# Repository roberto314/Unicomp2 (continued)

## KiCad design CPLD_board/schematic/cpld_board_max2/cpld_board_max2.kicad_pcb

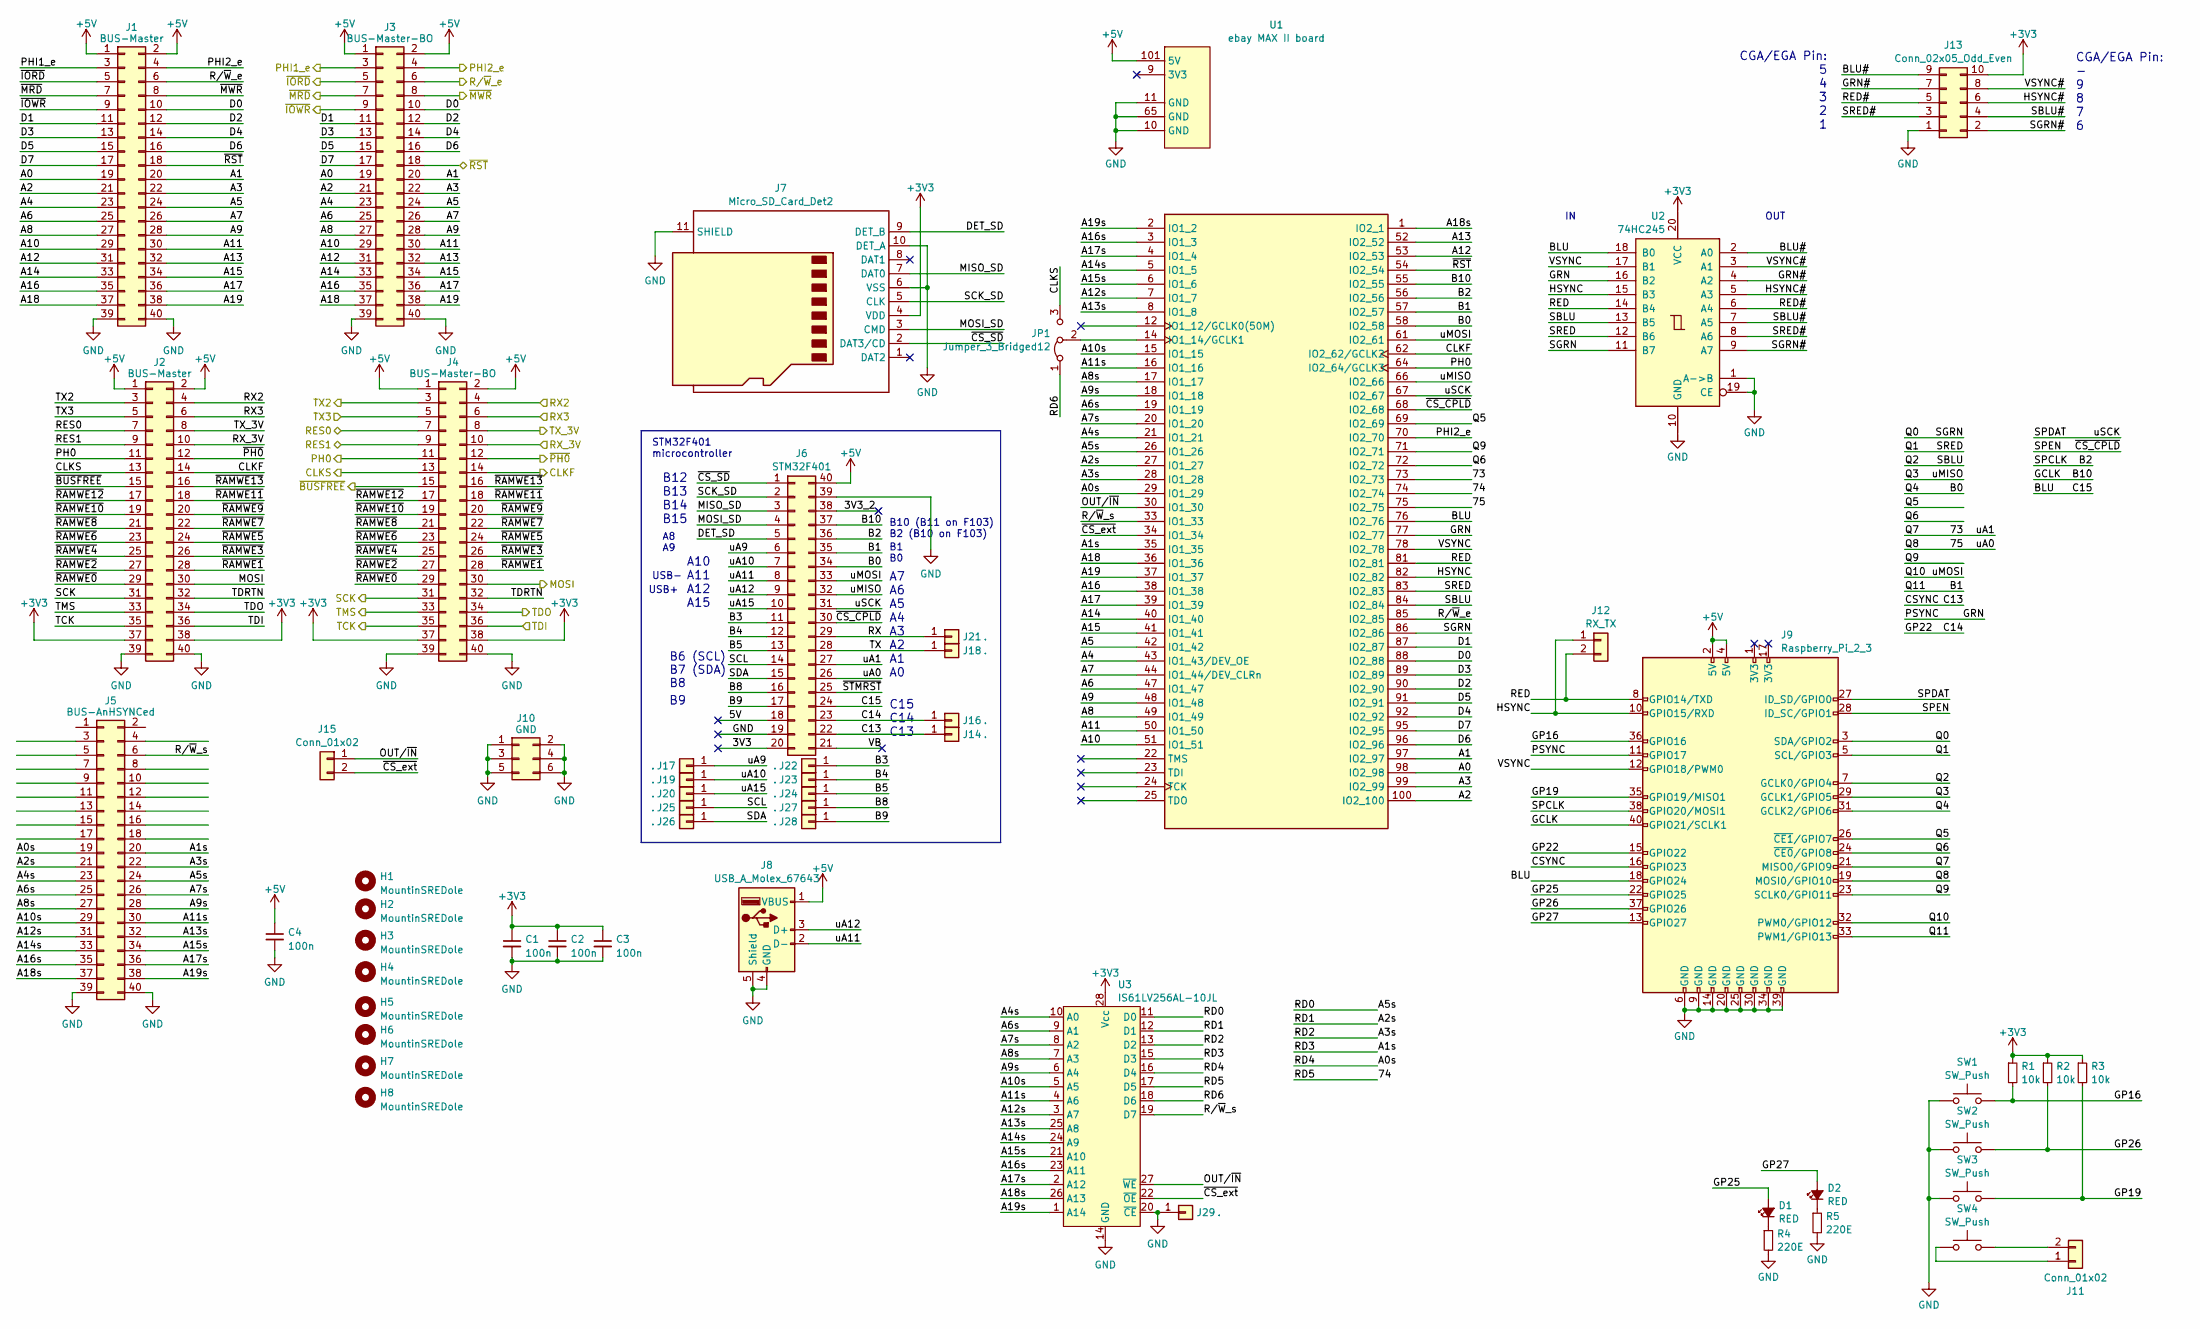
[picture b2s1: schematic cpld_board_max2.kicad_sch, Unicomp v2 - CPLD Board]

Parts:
C1, C2, C3, C4: 100n; C_1206_3216Metric
D1, D2: RED; LED_D3.0mm
H1, H2, H3, H4, H5, H6, H7, H8: MountinSREDole; MountingHole_3.2mm_M3
J1, J2: BUS-Master; PinSocket_2x20_P2.54mm_Vertical
J3, J4: BUS-Master-BO; PinSocket_2x20_P2.54mm_Vertical
J5: BUS-AnHSYNCed; PinHeader_2x20_P2.54mm_Horizontal
J6: STM32F401; DIP-40_W15.24mm_Socket_LongPads
J7: Micro_SD_Card_Det2; microSD_HC_Hirose_DM3D-SF
J8: USB_A_Molex_67643; USB_A_Molex_67643_Horizontal
J9: Raspberry_Pi_2_3; Raspberry_Pi_Zero_Socketed_THT_FaceDown_MountingHoles
J10: GND; PinHeader_2x03_P2.54mm_Vertical
J11, J15: Conn_01x02; PinHeader_1x02_P2.54mm_Vertical
J12: RX_TX; PinHeader_1x02_P2.54mm_Vertical
J13: Conn_02x05_Odd_Even; PinHeader_2x05_P2.54mm_Vertical
J14, J16, J17, J18, J19, J20, J21, J22, J23, J24, J25, J26, J27, J28, J29: .; PinHeader_1x01_P2.00mm_Vertical
JP1: Jumper_3_Bridged12; SolderJumper-3_P1.3mm_Bridged12_RoundedPad1.0x1.5mm
R1, R2, R3: 10k; R_1206_3216Metric_Pad1.30x1.75mm_HandSolder
R4, R5: 220E; R_1206_3216Metric_Pad1.30x1.75mm_HandSolder
SW1, SW2, SW3, SW4: SW_Push; SW_PUSH_6mm_H4.3mm
U1: ebay MAX II board; ebay-MAX_II_board
U2: 74HC245; SO-20_5.3x12.6mm_P1.27mm
U3: IS61LV256AL-10JL; SOIC-28W_7.5x17.9mm_P1.27mm

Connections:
+3V3: C1.1, C2.1, C3.1, J2.37, J2.38, J4.37, J4.38, J7.4 (VDD), J13.10, R1.1, R2.1, R3.1, U2.20 (VCC), U3.28 (Vcc)
+5V: C4.1, J1.1, J1.2, J2.1, J2.2, J3.1, J3.2, J4.1, J4.2, J6.40, J8.1 (VBUS), J9.2 (5V), J9.4 (5V), U1.101 (5V)
/3V3: J6.20
/3V3_2: J6.38
/5V: J6.18
/73: J6.27, J9.21 (MISO0/GPIO9), U1.73 (IO2_73)
/74: U1.74 (IO2_74), U3.17 (D5)
/75: J6.26, J9.19 (MOSI0/GPIO10), U1.75 (IO2_75)
/A0: J1.19, J3.19, U1.98 (IO2_98)
/A0s: J5.19, U1.29 (IO1_29), U3.16 (D4)
/A1: J1.20, J3.20, U1.97 (IO2_97)
/A1s: J5.20, U1.35 (IO1_35), U3.15 (D3)
/A2: J1.21, J3.21, U1.100 (IO2_100)
/A2s: J5.21, U1.27 (IO1_27), U3.12 (D1)
/A3: J1.22, J3.22, U1.99 (IO2_99)
/A3s: J5.22, U1.28 (IO1_28), U3.13 (D2)
/A4: J1.23, J3.23, U1.43 (IO1_43/DEV_OE)
/A4s: J5.23, U1.21 (IO1_21), U3.10 (A0)
/A5: J1.24, J3.24, U1.42 (IO1_42)
/A5s: J5.24, U1.26 (IO1_26), U3.11 (D0)
/A6: J1.25, J3.25, U1.47 (IO1_47)
/A6s: J5.25, U1.19 (IO1_19), U3.9 (A1)
/A7: J1.26, J3.26, U1.44 (IO1_44/DEV_CLRn)
/A7s: J5.26, U1.20 (IO1_20), U3.8 (A2)
/A8: J1.27, J3.27, U1.49 (IO1_49)
/A8s: J5.27, U1.17 (IO1_17), U3.7 (A3)
/A9: J1.28, J3.28, U1.48 (IO1_48)
/A9s: J5.28, U1.18 (IO1_18), U3.6 (A4)
/A10: J1.29, J3.29, U1.51 (IO1_51)
/A10s: J5.29, U1.15 (IO1_15), U3.5 (A5)
/A11: J1.30, J3.30, U1.50 (IO1_50)
/A11s: J5.30, U1.16 (IO1_16), U3.4 (A6)
/A12: J1.31, J3.31, U1.53 (IO2_53)
/A12s: J5.31, U1.7 (IO1_7), U3.3 (A7)
/A13: J1.32, J3.32, U1.52 (IO2_52)
/A13s: J5.32, U1.8 (IO1_8), U3.25 (A8)
/A14: J1.33, J3.33, U1.40 (IO1_40)
/A14s: J5.33, U1.5 (IO1_5), U3.24 (A9)
/A15: J1.34, J3.34, U1.41 (IO1_41)
/A15s: J5.34, U1.6 (IO1_6), U3.21 (A10)
/A16: J1.35, J3.35, U1.38 (IO1_38)
/A16s: J5.35, U1.3 (IO1_3), U3.23 (A11)
/A17: J1.36, J3.36, U1.39 (IO1_39)
/A17s: J5.36, U1.4 (IO1_4), U3.2 (A12)
/A18: J1.37, J3.37, U1.36 (IO1_36)
/A18s: J5.37, U1.1 (IO2_1), U3.26 (A13)
/A19: J1.38, J3.38, U1.37 (IO1_37)
/A19s: J5.38, U1.2 (IO1_2), U3.1 (A14)
/B0: J6.34, J9.31 (GCLK2/GPIO6), U1.58 (IO2_58)
/B1: J6.35, J9.33 (PWM1/GPIO13), U1.57 (IO2_57)
/B2: J6.36, J9.38 (GPIO20/MOSI1), U1.56 (IO2_56)
/B3: J6.11, J22.1
/B4: J6.12, J23.1
/B5: J6.13, J24.1
/B8: J6.16, J27.1
/B9: J6.17, J28.1
/B10: J6.37, J9.40 (GPIO21/SCLK1), U1.55 (IO2_55)
/BLU: J6.24, J9.18 (GPIO24), U1.76 (IO2_76), U2.18 (B0)
/BLU#: J13.9, U2.2 (A0)
/C13: J6.22, J9.16 (GPIO23), J14.1
/C14: J6.23, J9.15 (GPIO22), J16.1
/CLKF: J2.14, J4.14, U1.62 (IO2_62/GCLK2)
/CLKS: J2.13, J4.13, JP1.3 (B)
/D0: J1.10, J3.10, U1.88 (IO2_88)
/D1: J1.11, J3.11, U1.87 (IO2_87)
/D2: J1.12, J3.12, U1.90 (IO2_90)
/D3: J1.13, J3.13, U1.89 (IO2_89)
/D4: J1.14, J3.14, U1.92 (IO2_92)
/D5: J1.15, J3.15, U1.91 (IO2_91)
/D6: J1.16, J3.16, U1.96 (IO2_96)
/D7: J1.17, J3.17, U1.95 (IO2_95)
/DET_SD: J6.5, J7.9 (DET_B)
/GP16: J9.36 (GPIO16), R1.2, SW1.2
/GP19: J9.35 (GPIO19/MISO1), R3.2, SW3.2
/GP25: D1.2 (A), J9.22 (GPIO25)
/GP26: J9.37 (GPIO26), R2.2, SW2.2
/GP27: D2.2 (A), J9.13 (GPIO27)
/GRN: J9.11 (GPIO17), U1.77 (IO2_77), U2.16 (B2)
/GRN#: J13.7, U2.4 (A2)
/HSYNC: J9.10 (GPIO15/RXD), J12.1, U1.82 (IO2_82), U2.15 (B3)
/HSYNC#: J13.6, U2.5 (A3)
/MISO_SD: J6.3, J7.7 (DAT0)
/MOSI: J2.30, J4.30
/MOSI_SD: J6.4, J7.3 (CMD)
/OUT/~IN: J15.1, U1.30 (IO1_30), U3.27 (~WE)
/PH0: J2.11, J4.11, U1.64 (IO2_64/GCLK3)
/PHI1_e: J1.3, J3.3
/PHI2_e: J1.4, J3.4, U1.70 (IO2_70)
/Q0: J9.3 (SDA/GPIO2), U1.86 (IO2_86), U2.11 (B7)
/Q1: J9.5 (SCL/GPIO3), U1.83 (IO2_83), U2.12 (B6)
/Q2: J9.7 (GCLK0/GPIO4), U1.84 (IO2_84), U2.13 (B5)
/Q3: J6.32, J9.29 (GCLK1/GPIO5), U1.66 (IO2_66)
/Q5: J9.26 (~CE1/GPIO7), U1.69 (IO2_69)
/Q6: J9.24 (~CE0/GPIO8), U1.72 (IO2_72)
/Q9: J9.23 (SCLK0/GPIO11), U1.71 (IO2_71)
/Q10: J6.33, J9.32 (PWM0/GPIO12), U1.61 (IO2_61)
/RD6: JP1.1 (A), U3.18 (D6)
/RED: J9.8 (GPIO14/TXD), J12.2, U1.81 (IO2_81), U2.14 (B4)
/RED#: J13.5, U2.6 (A4)
/RES0: J2.7, J4.7
/RES1: J2.9, J4.9
/RX: J6.29, J21.1; also elsewhere on the board
/RX2: J2.4, J4.4
/RX3: J2.6, J4.6
/RX_3V: J2.10, J4.10
/R/~W_e: J1.6, J3.6, U1.85 (IO2_85)
/R/~W_s: J5.6, U1.33 (IO1_33), U3.19 (D7)
/SBLU#: J13.4, U2.7 (A5)
/SCK: J2.31, J4.31
/SCK_SD: J6.2, J7.5 (CLK)
/SCL: J6.14, J25.1
/SDA: J6.15, J26.1
/SGRN#: J13.2, U2.9 (A7)
/SPDAT: J6.31, J9.27 (ID_SD/GPIO0), U1.67 (IO2_67)
/SPEN: J6.30, J9.28 (ID_SC/GPIO1), U1.68 (IO2_68)
/SRED#: J13.3, U2.8 (A6)
/TCK: J2.35, J4.35
/TDI: J2.36, J4.36
/TDO: J2.34, J4.34
/TDRTN: J2.32, J4.32
/TMS: J2.33, J4.33
/TX: J6.28, J18.1
/TX2: J2.3, J4.3
/TX3: J2.5, J4.5
/TX_3V: J2.8, J4.8
/VB: J6.21
/VSYNC: J9.12 (GPIO18/PWM0), U1.78 (IO2_78), U2.17 (B1)
/VSYNC#: J13.8, U2.3 (A1)
/uA9: J6.6, J17.1
/uA10: J6.7, J19.1
/uA11: J6.8, J8.2 (D-)
/uA12: J6.9, J8.3 (D+)
/uA15: J6.10, J20.1
/~BUSFREE: J2.15, J4.15
/~CS_SD: J6.1, J7.2 (DAT3/CD)
/~CS_ext: J15.2, U1.34 (IO1_34), U3.22 (~OE)
/~IORD: J1.5, J3.5
/~IOWR: J1.9, J3.9
/~MRD: J1.7, J3.7
/~MWR: J1.8, J3.8
/~PH0: J2.12, J4.12
/~RAMWE0: J2.29, J4.29
/~RAMWE1: J2.28, J4.28
/~RAMWE2: J2.27, J4.27
/~RAMWE3: J2.26, J4.26
/~RAMWE4: J2.25, J4.25
/~RAMWE5: J2.24, J4.24
/~RAMWE6: J2.23, J4.23
/~RAMWE7: J2.22, J4.22
/~RAMWE8: J2.21, J4.21
/~RAMWE9: J2.20, J4.20
/~RAMWE10: J2.19, J4.19
/~RAMWE11: J2.18, J4.18
/~RAMWE12: J2.17, J4.17
/~RAMWE13: J2.16, J4.16
/~RST: J1.18, J3.18, U1.54 (IO2_54)
/~STMRST: J6.25
GND: C1.2, C2.2, C3.2, C4.2, J1.39, J1.40, J2.39, J2.40, J3.39, J3.40, J4.39, J4.40, J5.39, J5.40, J6.19, J6.39, J7.6 (VSS), J7.10 (DET_A), J7.11 (SHIELD), J8.4 (GND), J8.5 (Shield), J9.6 (GND), J9.9 (GND), J9.14 (GND), J9.20 (GND), J9.25 (GND), J9.30 (GND), J9.34 (GND), J9.39 (GND), J10.1, J10.2, J10.3, J10.4, J10.5, J10.6, J13.1, J29.1, R4.2, R5.2, SW1.1, SW2.1, SW3.1, U1.10 (GND), U1.11 (GND), U1.65 (GND), U2.1 (A->B), U2.10 (GND), U2.19 (CE), U3.14 (GND), U3.20 (~CE)
unnamed: D1.1 (K), R4.1
unnamed: D2.1 (K), R5.1
unnamed: J11.1, SW4.1
unnamed: J11.2, SW4.2
unnamed: JP1.2 (C), U1.14 (IO1_14/GCLK1)

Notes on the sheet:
OUT
USB+
STM32F401 microcontroller
B1 B0
CGA/EGA Pin: 5 4 3 2 1
A7 A6 A5 A4 A3 A2 A1 A0
B6 (SCL) B7 (SDA) B8
CGA/EGA Pin: - 9 8 7 6
B12 B13 B14 B15
A8 A9
C15 C14 C13
USB-
B10 (B11 on F103) B2 (B10 on F103)
A10 A11 A12 A15

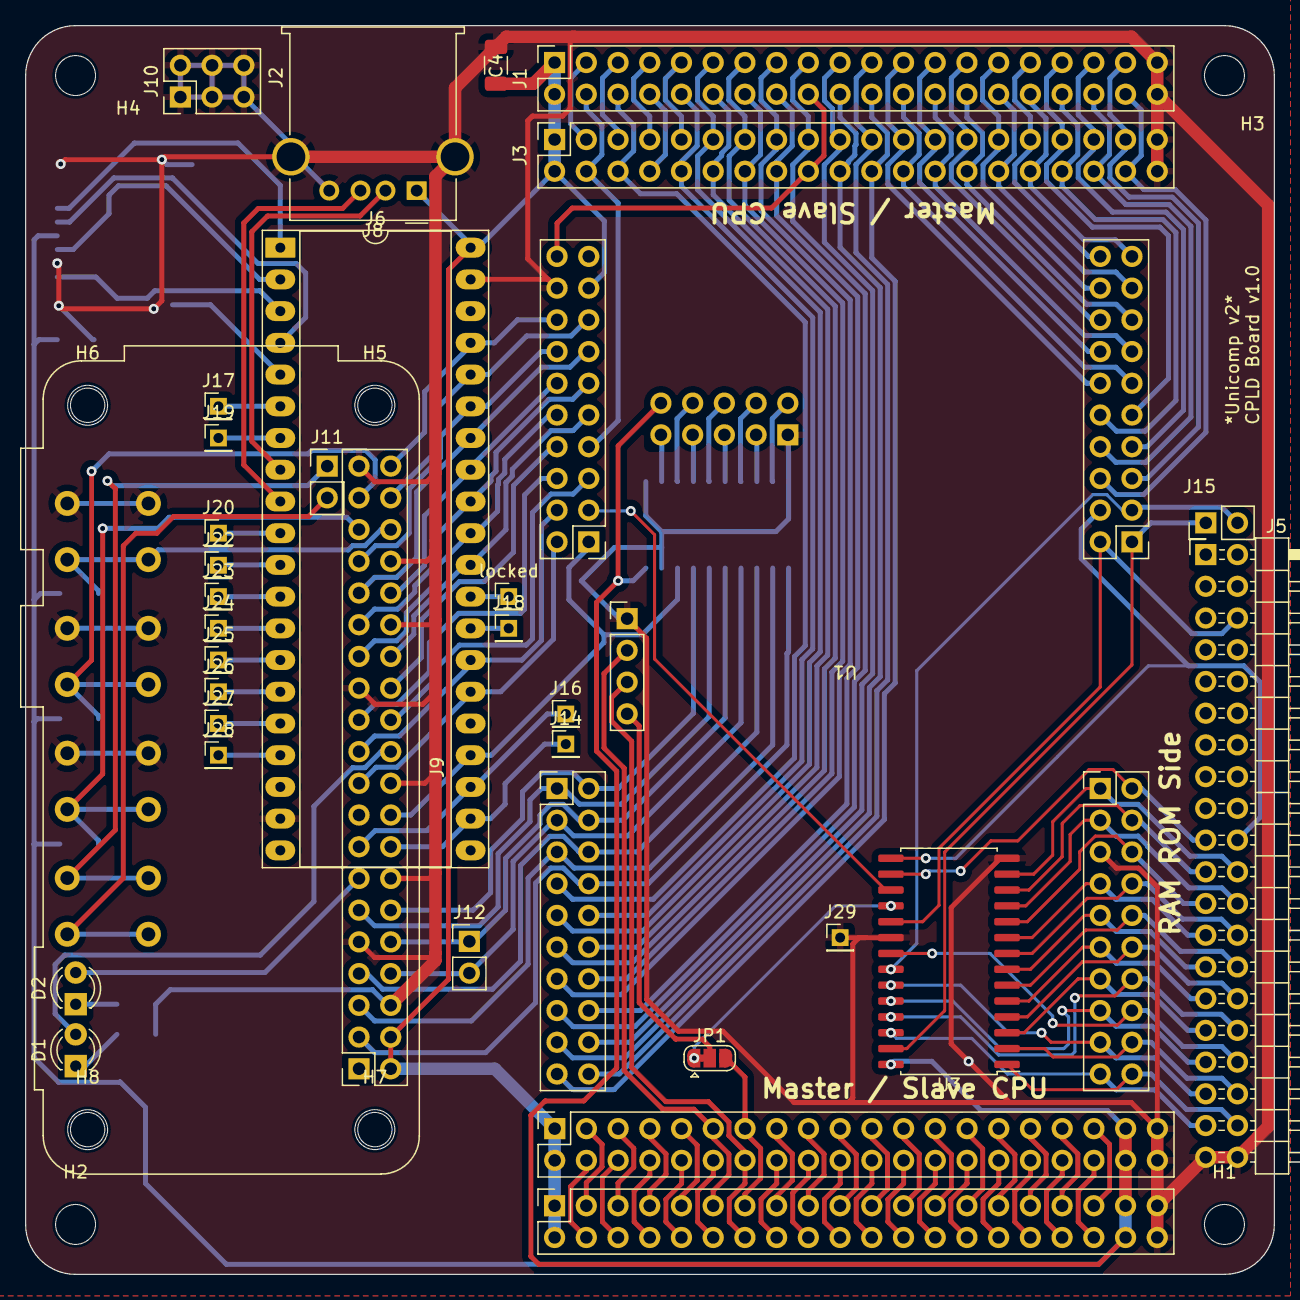
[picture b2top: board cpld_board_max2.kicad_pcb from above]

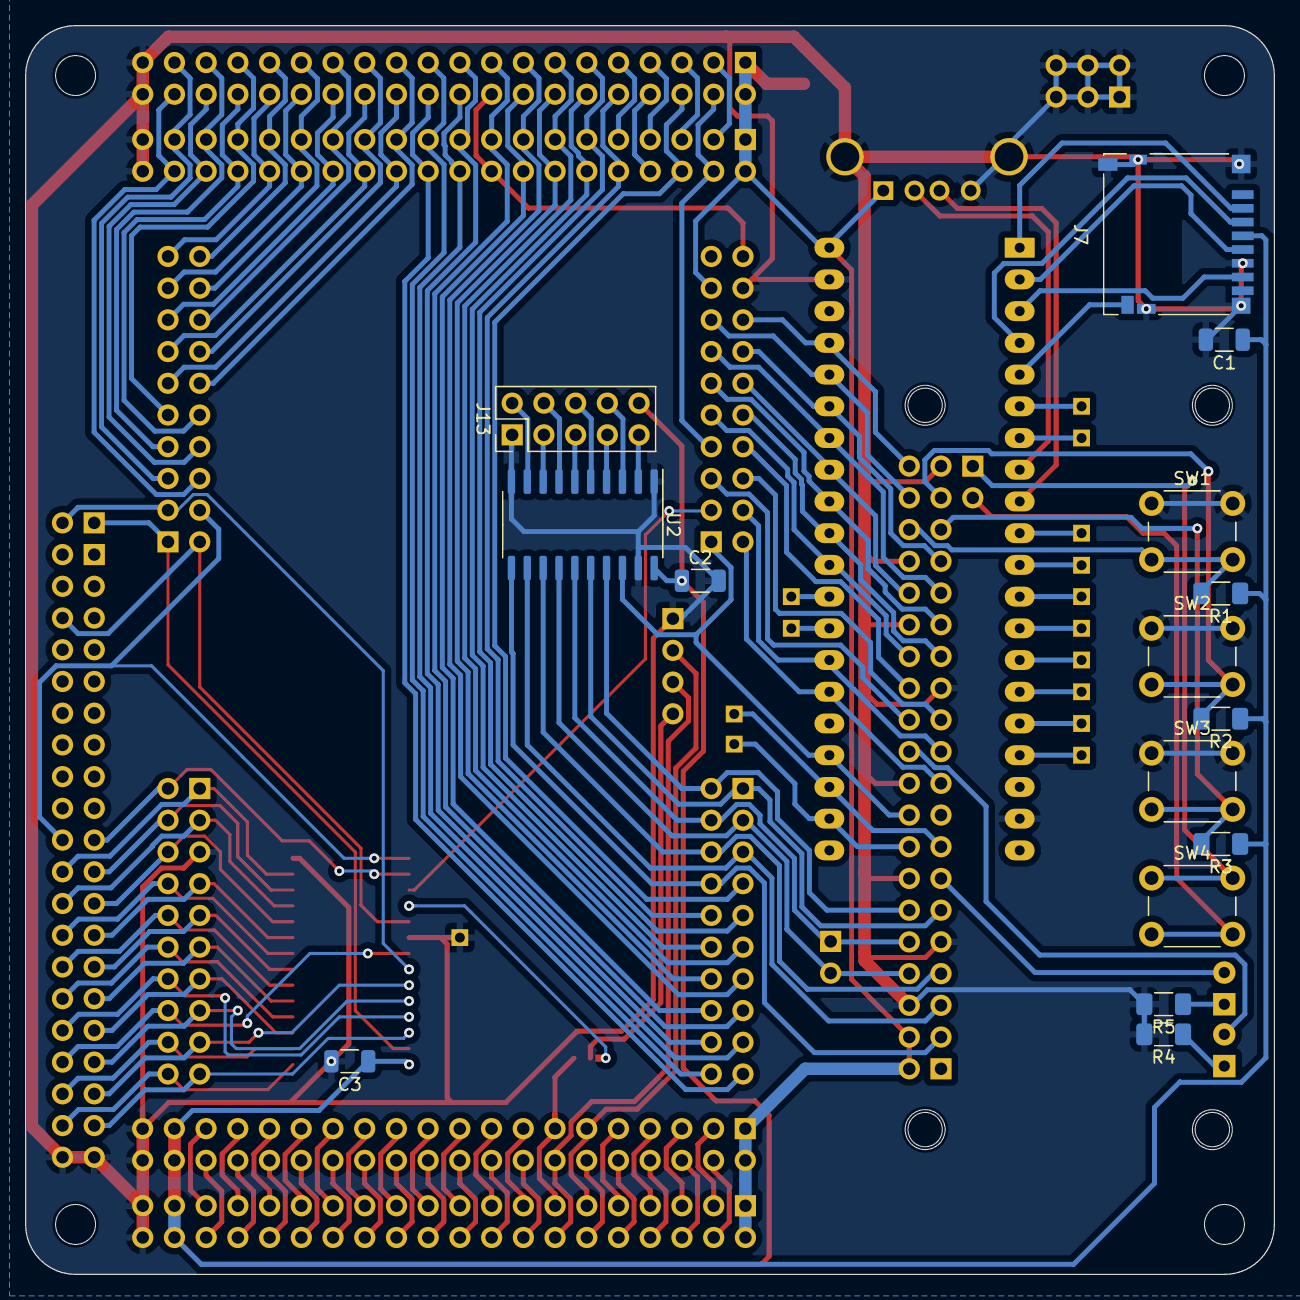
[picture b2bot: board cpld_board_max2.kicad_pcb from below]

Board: 2 copper layers, 100.0 x 100.0 mm, 56 parts (15 on the bottom side), 158 nets.

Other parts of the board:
locked: .; PinHeader_1x01_P2.00mm_Vertical

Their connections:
/RX: locked.1; also elsewhere on the board

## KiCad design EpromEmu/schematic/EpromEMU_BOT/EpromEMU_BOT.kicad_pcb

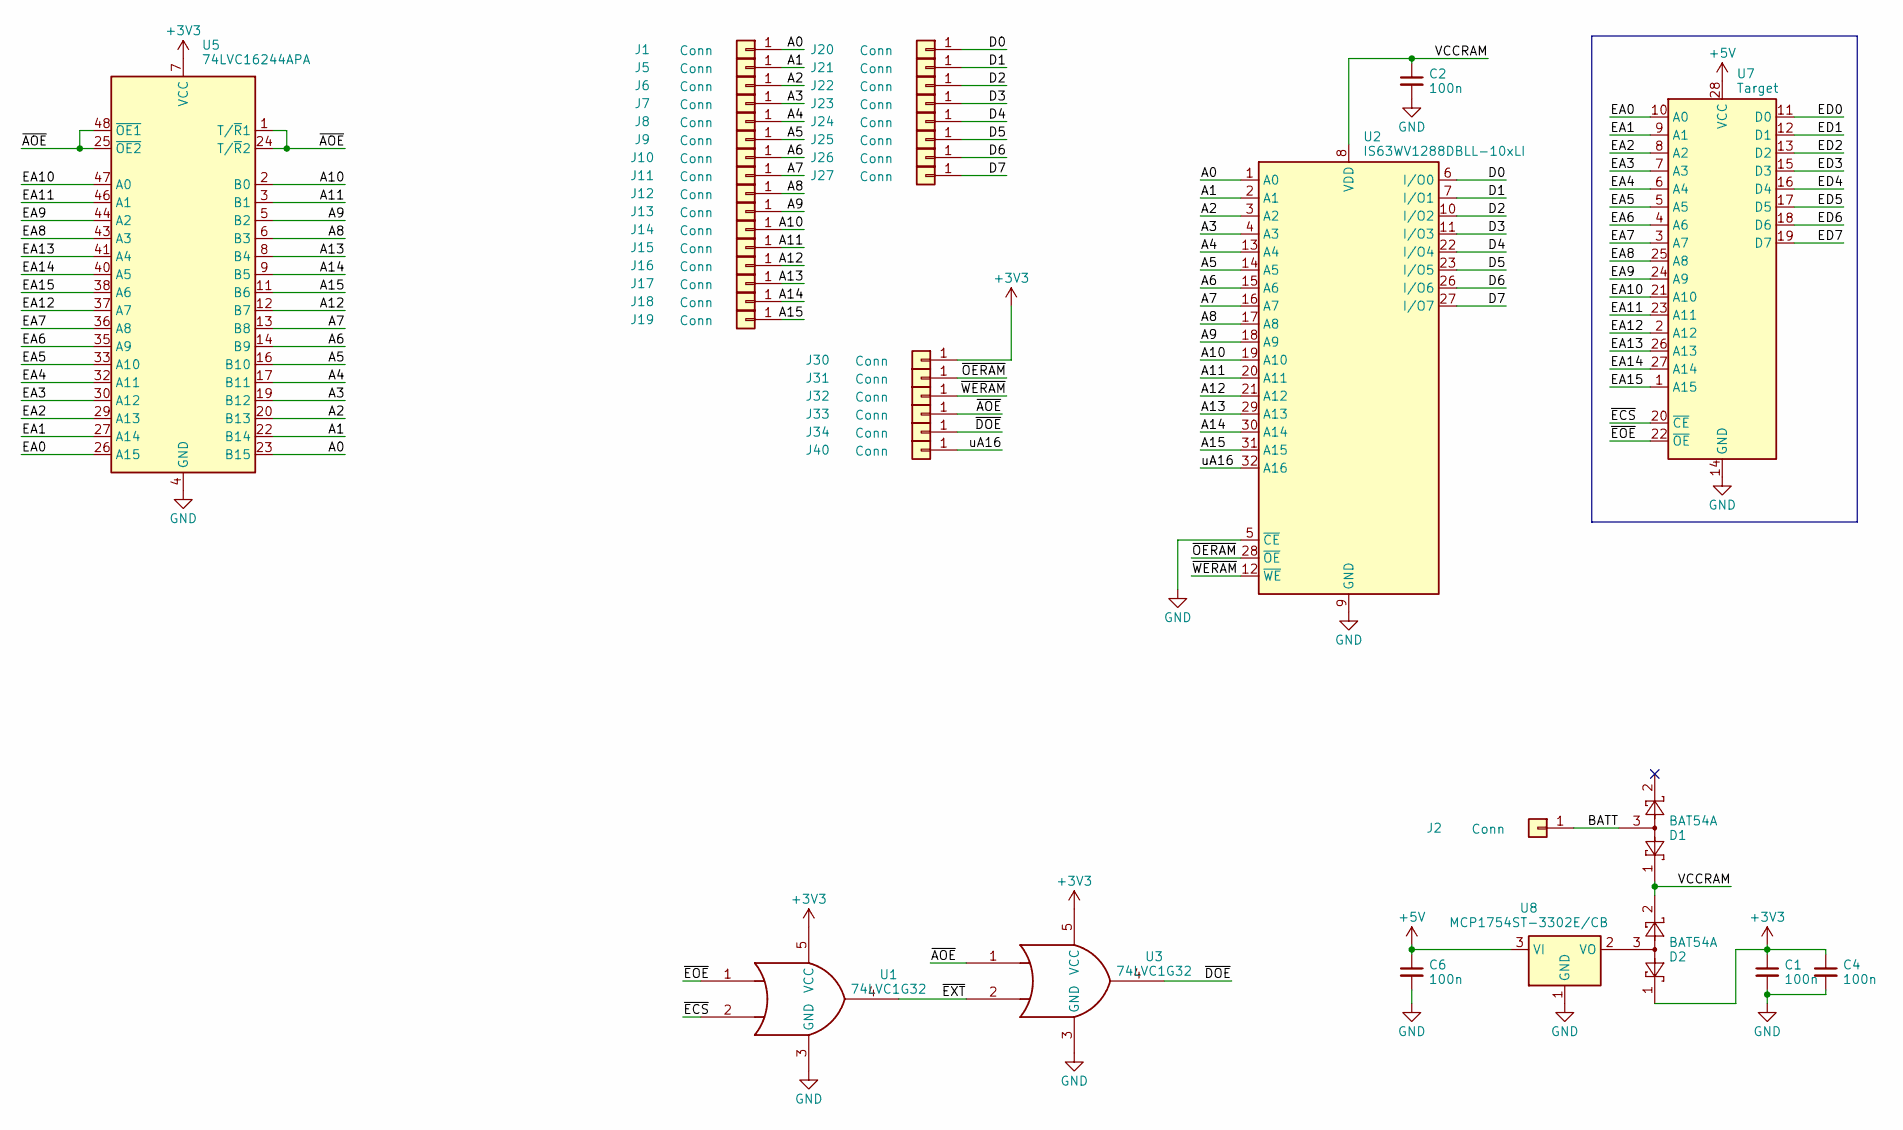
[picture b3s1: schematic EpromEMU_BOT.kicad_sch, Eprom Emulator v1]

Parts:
C1, C2, C4, C6: 100n; C_0805_2012Metric
D1, D2: BAT54A; SOT-23
J1, J2, J5, J6, J7, J8, J9, J10, J11, J12, J13, J14, J15, J16, J17, J18, J19, J20, J21, J22, J23, J24, J25, J26, J27, J30, J31, J32, J33, J34, J40: Conn; PTH_0.8_0.5mm
U1, U3: 74LVC1G32; SOT-23-5_HandSoldering
U2: IS63WV1288DBLL-10xLI; TSOP-I-32_11.8x8mm_P0.5mm
U5: 74LVC16244APA; TSSOP-48_6.1x12.5mm_P0.5mm
U7: Target; DIP-28_W15.24mm
U8: MCP1754ST-3302E/CB; SOT-23

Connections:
+3V3: C1.1, C4.1, D2.1, J30.1, U1.5 (VCC), U3.5 (VCC), U5.7 (VCC), U5.18 (VCC), U5.31 (VCC), U5.42 (VCC)
+5V: C6.1, U7.28 (VCC), U8.3 (VI)
/A0: J1.1, U2.1 (A0), U5.23 (B15)
/A1: J5.1, U2.2 (A1), U5.22 (B14)
/A2: J6.1, U2.3 (A2), U5.20 (B13)
/A3: J7.1, U2.4 (A3), U5.19 (B12)
/A4: J8.1, U2.13 (A4), U5.17 (B11)
/A5: J9.1, U2.14 (A5), U5.16 (B10)
/A6: J10.1, U2.15 (A6), U5.14 (B9)
/A7: J11.1, U2.16 (A7), U5.13 (B8)
/A8: J12.1, U2.17 (A8), U5.6 (B3)
/A9: J13.1, U2.18 (A9), U5.5 (B2)
/A10: J14.1, U2.19 (A10), U5.2 (B0)
/A11: J15.1, U2.20 (A11), U5.3 (B1)
/A12: J16.1, U2.21 (A12), U5.12 (B7)
/A13: J17.1, U2.29 (A13), U5.8 (B4)
/A14: J18.1, U2.30 (A14), U5.9 (B5)
/A15: J19.1, U2.31 (A15), U5.11 (B6)
/BATT: D1.3, J2.1
/D0: J20.1, U2.6 (I/O0)
/D1: J21.1, U2.7 (I/O1)
/D2: J22.1, U2.10 (I/O2)
/D3: J23.1, U2.11 (I/O3)
/D4: J24.1, U2.22 (I/O4)
/D5: J25.1, U2.23 (I/O5)
/D6: J26.1, U2.26 (I/O6)
/D7: J27.1, U2.27 (I/O7)
/EA0: U5.26 (A15), U7.10 (A0)
/EA1: U5.27 (A14), U7.9 (A1)
/EA2: U5.29 (A13), U7.8 (A2)
/EA3: U5.30 (A12), U7.7 (A3)
/EA4: U5.32 (A11), U7.6 (A4)
/EA5: U5.33 (A10), U7.5 (A5)
/EA6: U5.35 (A9), U7.4 (A6)
/EA7: U5.36 (A8), U7.3 (A7)
/EA8: U5.43 (A3), U7.25 (A8)
/EA9: U5.44 (A2), U7.24 (A9)
/EA10: U5.47 (A0), U7.21 (A10)
/EA11: U5.46 (A1), U7.23 (A11)
/EA12: U5.37 (A7), U7.2 (A12)
/EA13: U5.41 (A4), U7.26 (A13)
/EA14: U5.40 (A5), U7.27 (A14)
/EA15: U5.38 (A6), U7.1 (A15)
/ED0: U7.11 (D0)
/ED1: U7.12 (D1)
/ED2: U7.13 (D2)
/ED3: U7.15 (D3)
/ED4: U7.16 (D4)
/ED5: U7.17 (D5)
/ED6: U7.18 (D6)
/ED7: U7.19 (D7)
/VCCRAM: C2.1, D1.1, D2.2, U2.8 (VDD), U2.24 (VDD)
/uA16: J40.1, U2.32 (A16)
/~AOE: J33.1, U3.1, U5.1 (T/~R1), U5.24 (T/~R2), U5.25 (~OE2), U5.48 (~OE1)
/~DOE: J34.1, U3.4
/~ECS: U1.2, U7.20 (~CE)
/~EOE: U1.1, U7.22 (~OE)
/~EXT: U1.4, U3.2
/~OERAM: J31.1, U2.28 (~OE)
/~WERAM: J32.1, U2.12 (~WE)
GND: C1.2, C2.2, C4.2, C6.2, U1.3 (GND), U2.5 (~CE), U2.9 (GND), U2.25 (GND), U3.3 (GND), U5.4 (GND), U5.10 (GND), U5.15 (GND), U5.21 (GND), U5.28 (GND), U5.34 (GND), U5.39 (GND), U5.45 (GND), U7.14 (GND), U8.1 (GND)
unnamed: D2.3, U8.2 (VO)

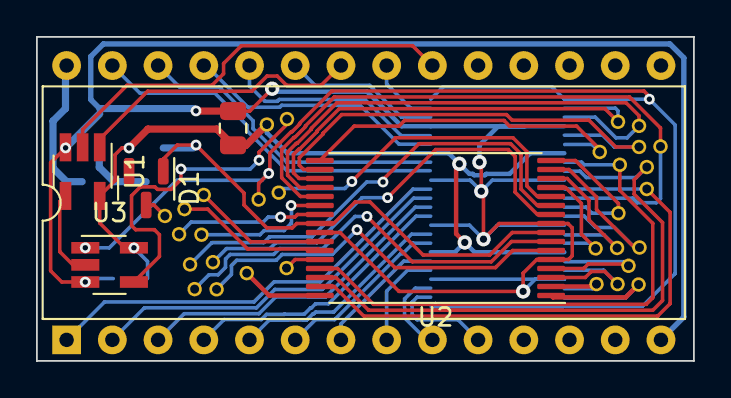
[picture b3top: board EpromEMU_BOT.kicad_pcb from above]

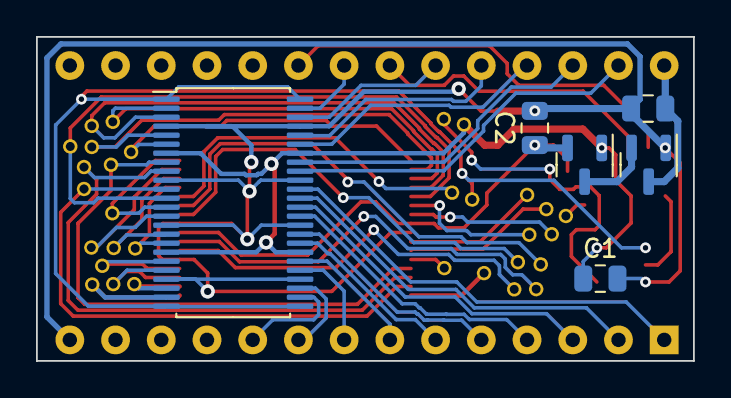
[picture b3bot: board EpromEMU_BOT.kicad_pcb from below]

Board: 2 copper layers, 36.5 x 18.0 mm, 43 parts (6 on the bottom side), 54 nets.

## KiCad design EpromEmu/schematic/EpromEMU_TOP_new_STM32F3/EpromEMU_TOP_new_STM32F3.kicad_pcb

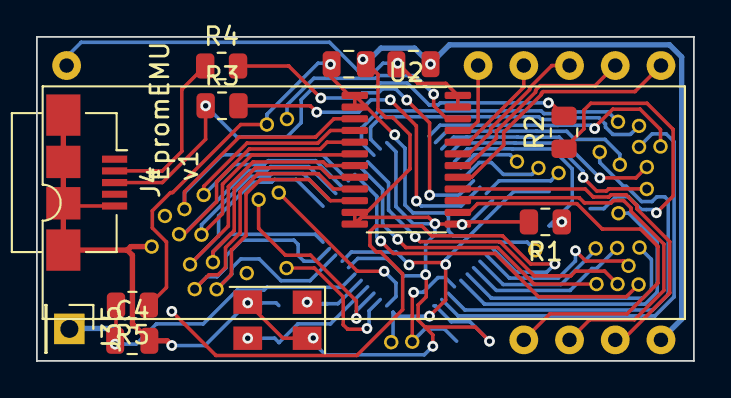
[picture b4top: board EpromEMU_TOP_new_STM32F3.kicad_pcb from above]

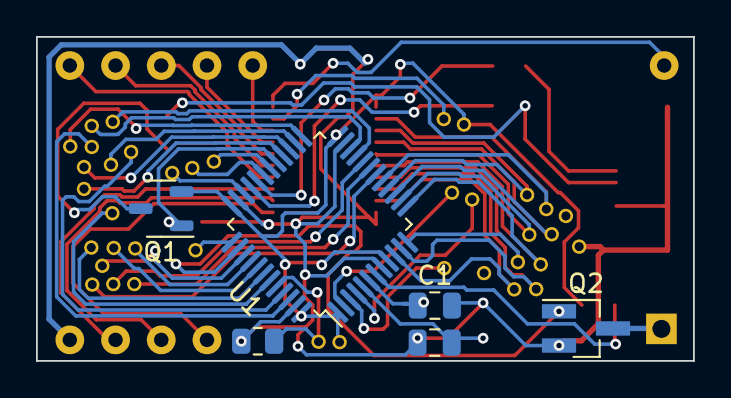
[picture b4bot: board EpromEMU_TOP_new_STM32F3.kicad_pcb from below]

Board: 2 copper layers, 36.5 x 18.0 mm, 57 parts (6 on the bottom side), 55 nets.

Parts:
C1, C3: C_Small; C_0805_2012Metric
C2, C4, C5: 100n; C_0805_2012Metric
J1, J5, J6, J7, J8, J9, J10, J11, J12, J13, J14, J15, J16, J17, J18, J19, J20, J21, J22, J23, J24, J25, J26, J27, J28, J29, J30, J31, J32, J33, J34, J36, J37, J38, J39, J40: Conn; PTH_0.8_0.5mm
J2, J3: DFU_En; PTH_0.8_0.5mm
J4: USB_B_Mini; USB_Micro-B_Amphenol_10104110_Horizontal
J35: Conn_01x01; PinHeader_1x01_P2.54mm_Vertical
Q1: BSH202; SOT-23-3
Q2: PMV450ENEAR; SOT-23_Handsoldering
R1, R6: 100k; R_0805_2012Metric
R2: 1k5; R_0805_2012Metric
R3, R4: 22E; R_0805_2012Metric
R5: 10k; R_0805_2012Metric
U1: STM32F303CCTx; LQFP-48_7x7mm_P0.5mm
U2: SN74LVCC3245APWR; TSSOP-24_4.4x7.8mm_P0.65mm
U7: Target; DIP-28_W15.24mm
Y1: 8M; Crystal_SMD_5032-4Pin_5.0x3.2mm

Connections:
+3V3: C5.1, J3.1, J30.1, Q1.2 (S), R5.1, U1.1 (VBAT), U1.9 (VDDA), U1.24 (VDD), U1.36 (VDD), U1.48 (VDD), U2.1 (VCCA), U2.2 (A->B)
+5V: C2.1, U2.23 (VCCB), U2.24 (VCCB), U7.28 (VCC)
/A0: J1.1, U1.18 (PB0)
/A1: J5.1, U1.19 (PB1)
/A2: J6.1, U1.20 (PB2)
/A3: J7.1, U1.39 (PB3)
/A4: J8.1, U1.40 (PB4)
/A5: J9.1, U1.41 (PB5)
/A6: J10.1, U1.42 (PB6)
/A7: J11.1, U1.43 (PB7)
/A8: J12.1, U1.45 (PB8)
/A9: J13.1, U1.46 (PB9)
/A10: J14.1, U1.21 (PB10)
/A11: J15.1, U1.22 (PB11)
/A12: J16.1, U1.25 (PB12)
/A13: J17.1, U1.26 (PB13)
/A14: J18.1, U1.27 (PB14)
/A15: J19.1, U1.28 (PB15)
/D0: J20.1, U1.10 (PA0), U2.10 (A7)
/D1: J21.1, U1.11 (PA1), U2.9 (A6)
/D2: J22.1, U1.12 (PA2), U2.8 (A5)
/D3: J23.1, U1.13 (PA3), U2.7 (A4)
/D4: J24.1, U1.14 (PA4), U2.6 (A3)
/D5: J25.1, U1.15 (PA5), U2.5 (A2)
/D6: J26.1, U1.16 (PA6), U2.4 (A1)
/D7: J27.1, U1.17 (PA7), U2.3 (A0)
/DM: R4.2, U1.32 (PA11)
/DP: R3.2, U1.33 (PA12)
/ED0: U2.14 (B7), U7.11 (D0)
/ED1: U2.15 (B6), U7.12 (D1)
/ED2: U2.16 (B5), U7.13 (D2)
/ED3: U2.17 (B4), U7.15 (D3)
/ED4: U2.18 (B3), U7.16 (D4)
/ED5: U2.19 (B2), U7.17 (D5)
/ED6: U2.20 (B1), U7.18 (D6)
/ED7: U2.21 (B0), U7.19 (D7)
/OSC0: C3.1, U1.5 (PF0), Y1.3
/OSC1: C1.1, U1.6 (PF1), Y1.1
/RX: J38.1, U1.31 (PA10)
/SWCLK: J39.1, U1.37 (PA14)
/SWDIO: J37.1, U1.34 (PA13)
/TX: J36.1, U1.30 (PA9)
/~AOE: J33.1, U1.4 (PC15)
/~DISC: Q1.1 (G), R1.1, U1.29 (PA8)
/~DOE: J34.1, U2.22 (CE)
/~OERAM: J31.1, U1.3 (PC14)
/~WERAM: J32.1, U1.2 (PC13)
/~extRST: J35.1, Q2.3 (D)
/~sRST: C4.1, R5.2, U1.7 (NRST)
GND: C1.2, C2.2, C3.2, C4.2, C5.2, J4.5 (GND), J4.6 (Shield), J29.1, Q2.2 (S), R1.2, R6.2, U1.8 (VSSA), U1.23 (VSS), U1.35 (VSS), U1.47 (VSS), U2.11 (GND), U2.12 (GND), U2.13 (GND), U7.14 (GND), Y1.2, Y1.4
unnamed: J2.1, R6.1, U1.44 (BOOT0)
unnamed: J4.3 (D+), R2.2, R3.1
unnamed: J4.2 (D-), R4.1
unnamed: Q1.3 (D), R2.1
unnamed: Q2.1 (G), U1.38 (PA15)
